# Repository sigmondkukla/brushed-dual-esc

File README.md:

# brushed-dual-esc
**Clarkson University Combat Robotics SPEED Team**

## Summary

Dual drive ESC for Clarkson Combat Robotics 1lb freshman PLAnt competition.
Supports two 3A brushed drive motors and includes a 5V 1A BEC output to power a receiver. 

## Details

The ESC implements an STM32C011 MCU to generate PWM for motor drivers from RX channel inputs while monitoring current, signal prescence (failsafe), and battery voltage UVLO.

With the 2026 revision of the ESC, XT30 wire-to-board connectors have been replaced with solder pads for leads to GNB A30 connectors.
An XT30 connector is still reccomended for the battery input.
The battery shall be a 2S or 3S LiPo battery; 4S is not supported based on cost optimization, though targeting a slightly higher cost (and larger size) by increasing capacitor specifications is a simple modification.
At 4S, the current from the 5V BEC output shall be kept to a minimum. 

The ESC expects two receiver channel outputs to be connected to the CH1 and CH2 inputs, which map directly to the DRV1 and DRV2 outputs. A 50 Hz (20 ms period) PWM signal (5V tolerated) with a duty cycle between 1000 us and 2000 us is needed, based on the outputs of the common FS-2A receiver.
A duty cycle of 1500 us is considered neutral, with lower duty cycles resulting in reverse operation and higher duty cycles corresponding to forward operation.

A 3A current limit has been configured with the 750-ohm resistors connected to IPROPI on each motor driver.
Above this current limit, the ESC will chop to avoid over current, despite the driver supporting up to 3.7A.
The ESC pairs well therefore with the [Repeat Mini Brushed Mk2](https://repeat-robotics.com/products/repeat-mini-brushed-mk2-1pcs), which has a stall current of 2A at 3S.

## Assembly

Assembly with a pick-and-place machine is reccomended for large volumes >= 10 units, though hand assembly is straightforward given the large motor driver, LDO, and passives packages.
The pick and place work file for a CHM-T36VA machine is included in the `pcb/fabrication` directory, though minor modifications may be necessary.
The DRV8231 ICs were not successfully picked by the machine so are set to be skipped, and the electrolytic capacitors were not attempted.
I loaded the 503 nozzle in tool 1 and the 505 nozzle in tool 2 for this job.

A clean paste image is necessary for successful soldering of the STM32 MCU.

## Programming

Programming is achieved through a Tag-Connect TC2030-CTX-NL pogo pins programmer cable which retails around $50, though can be purchased on Aliexpress for about half the price.
I'm using it in conjunction with a Segger J-Link EDU mini though any debugger can be used.
SWO is not available on STM32C0 so one of the six pins is unused.

The firmware may be programmed using [STM32CubeProg](https://www.st.com/en/development-tools/stm32cubeprog.html) and the firmware ELF file included in the most recent release on GitHub.

## Images
### Screenshots

### Photos

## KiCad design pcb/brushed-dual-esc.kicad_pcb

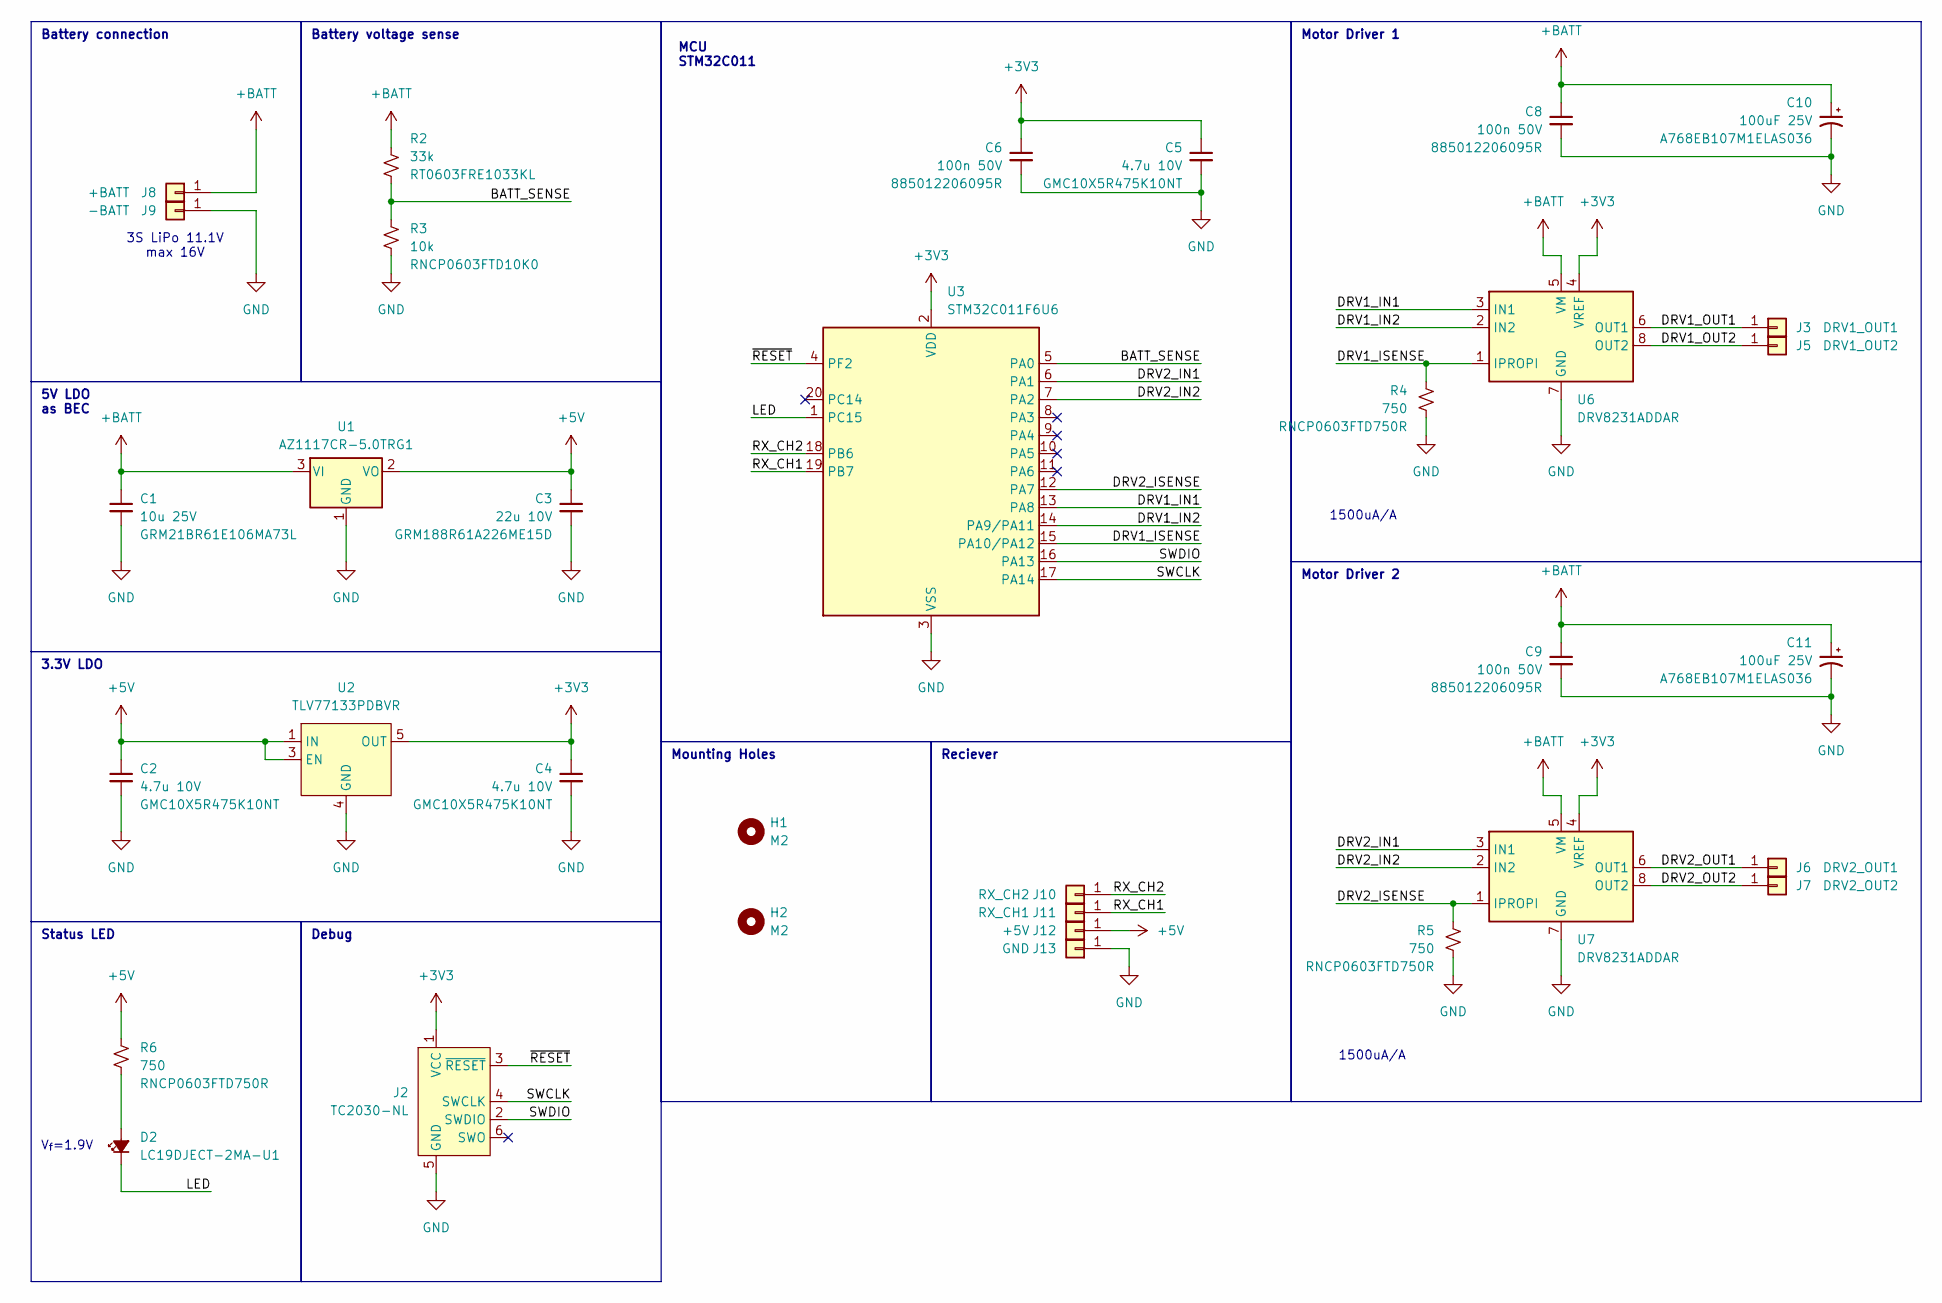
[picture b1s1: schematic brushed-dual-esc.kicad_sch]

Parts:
C1: 10u 25V; C_0805_2012Metric; MPN GRM21BR61E106MA73L
C2, C4, C5: 4.7u 10V; C_0603_1608Metric; MPN GMC10X5R475K10NT
C3: 22u 10V; C_0603_1608Metric; MPN GRM188R61A226ME15D
C6, C8, C9: 100n 50V; C_0603_1608Metric; MPN 885012206095R
C10, C11: 100uF 25V; CP_Elec_6.3x5.7; MPN A768EB107M1ELAS036
D2: LC19DJECT-2MA-U1; LED_0603_1608Metric; MPN LC19DJECT-2MA-U1
H1, H2: M2; MountingHole_2.2mm_M2
J2: TC2030-NL; Tag-Connect_TC2030-IDC-NL_2x03_P1.27mm_Vertical
J3: DRV1_OUT1; SolderWirePad_1x01_SMD_2x4mm
J5: DRV1_OUT2; SolderWirePad_1x01_SMD_2x4mm
J6: DRV2_OUT1; SolderWirePad_1x01_SMD_2x4mm
J7: DRV2_OUT2; SolderWirePad_1x01_SMD_2x4mm
J8: +BATT; SolderWirePad_1x01_SMD_2x4mm
J9: -BATT; SolderWirePad_1x01_SMD_2x4mm
J10: RX_CH2; SolderWirePad_1x01_SMD_1x2mm
J11: RX_CH1; SolderWirePad_1x01_SMD_1x2mm
J12: +5V; SolderWirePad_1x01_SMD_1x2mm
J13: GND; SolderWirePad_1x01_SMD_1x2mm
R2: 33k; R_0603_1608Metric; MPN RT0603FRE1033KL
R3: 10k; R_0603_1608Metric; MPN RNCP0603FTD10K0
R4, R5, R6: 750; R_0603_1608Metric; MPN RNCP0603FTD750R
U1: AZ1117CR-5.0TRG1; SOT-89-3; MPN AZ1117CR-5.0TRG1
U2: TLV77133PDBVR; SOT-23-5; MPN TLV77133PDBVR
U3: STM32C011F6U6; ST_UFQFPN-20_3x3mm_P0.5mm; MPN STM32C011F6U6
U6, U7: DRV8231ADDAR; Texas_HSOP-8-1EP_3.9x4.9mm_P1.27mm; MPN DRV8231ADDAR

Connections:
+3V3: C4.1, C5.1, C6.1, J2.1 (VCC), U2.5 (OUT), U3.2 (VDD), U6.4 (VREF), U7.4 (VREF)
+5V: C2.1, C3.1, J12.1 (Pin_1_1), R6.1, U1.2 (VO), U2.1 (IN), U2.3 (EN)
+BATT: C1.1, C8.1, C9.1, C10.1, C11.1, J8.1 (Pin_1_1), R2.1, U1.3 (VI), U6.5 (VM), U7.5 (VM)
/BATT_SENSE: R2.2, R3.1, U3.5 (PA0)
/DRV1_IN1: U3.13 (PA8), U6.3 (IN1)
/DRV1_IN2: U3.14 (PA9/PA11), U6.2 (IN2)
/DRV1_ISENSE: R4.1, U3.15 (PA10/PA12), U6.1 (IPROPI)
/DRV1_OUT1: J3.1 (Pin_1_1), U6.6 (OUT1)
/DRV1_OUT2: J5.1 (Pin_1_1), U6.8 (OUT2)
/DRV2_IN1: U3.6 (PA1), U7.3 (IN1)
/DRV2_IN2: U3.7 (PA2), U7.2 (IN2)
/DRV2_ISENSE: R5.1, U3.12 (PA7), U7.1 (IPROPI)
/DRV2_OUT1: J6.1 (Pin_1_1), U7.6 (OUT1)
/DRV2_OUT2: J7.1 (Pin_1_1), U7.8 (OUT2)
/LED: D2.1 (K), U3.1 (PC15)
/RX_CH1: J11.1 (Pin_1_1), U3.19 (PB7)
/RX_CH2: J10.1 (Pin_1_1), U3.18 (PB6)
/SWCLK: J2.4 (SWCLK), U3.17 (PA14)
/SWDIO: J2.2 (SWDIO), U3.16 (PA13)
/~RESET: J2.3 (~RESET), U3.4 (PF2)
GND: C1.2, C2.2, C3.2, C4.2, C5.2, C6.2, C8.2, C9.2, C10.2, C11.2, J2.5 (GND), J9.1 (Pin_1_1), J13.1 (Pin_1_1), R3.2, R4.2, R5.2, U1.1 (GND), U2.4 (GND), U3.3 (VSS), U6.7 (GND), U6.9 (GND), U7.7 (GND), U7.9 (GND)
unnamed: D2.2 (A), R6.2

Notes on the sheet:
3.3V LDO
Status LED
Motor Driver 1
Motor Driver 2
Mounting Holes
1500uA/A
5V LDO as BEC
V_{f}=1.9V
Battery connection
Battery voltage sense
MCU STM32C011
3S LiPo 11.1V max 16V
Reciever
Debug

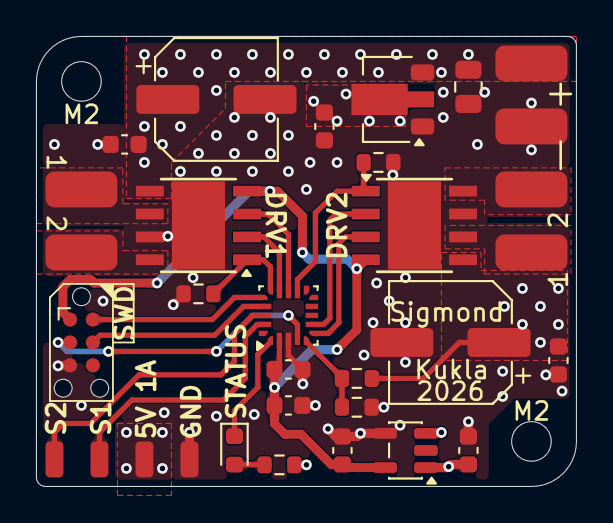
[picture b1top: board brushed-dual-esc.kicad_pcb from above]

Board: 2 copper layers, 30.0 x 25.0 mm, 34 parts (0 on the bottom side), 22 nets.

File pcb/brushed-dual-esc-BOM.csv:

"Reference","Qty","Value","MPN"
"C1","1","10µF 25V","GRM21BR61E106MA73L"
"C2,C4,C5","3","4.7u 10V","GMC10X5R475K10NT"
"C3","1","22uF 10V","GRM188R61A226ME15D"
"C6,C8,C9","3","100n 50V","885012206095R"
"C10,C11","2","100uF 25V","A768EB107M1ELAS036"
"D2","1","Vf=1.9V","LC19DJECT-2MA-U1"
"R2","1","33k","RT0603FRE1033KL"
"R3","1","10k","RNCP0603FTD10K0"
"R4,R5,R6","3","750","RNCP0603FTD750R"
"U1","1","AZ1117CR-5.0TRG1","AZ1117CR-5.0TRG1"
"U2","1","TLV77133PDBVR","TLV77133PDBVR"
"U3","1","STM32C011F6U6","STM32C011F6U6"
"U6,U7","2","DRV8231ADDAR","DRV8231ADDAR"

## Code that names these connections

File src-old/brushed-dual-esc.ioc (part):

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Mcu.Name=STM32C011F(4-6)Ux
Mcu.Package=UFQFPN20
Mcu.UserName=STM32C011F4Ux
PA0.GPIOParameters=GPIO_PuPd,GPIO_Label,GPIO_Mode
PA0.GPIO_Label=BATT_SENSE
PA0.GPIO_Mode=GPIO_MODE_ANALOG
PA0.GPIO_PuPd=GPIO_NOPULL
PA0.Mode=IN0
PA0.Signal=ADC1_IN0
PA1.GPIOParameters=GPIO_PuPd,GPIO_Label
PA1.GPIO_Label=DRV2_IN1
PA1.GPIO_PuPd=GPIO_PULLDOWN
PA1.Signal=S_TIM1_CH2
PA11\ [PA9].GPIOParameters=GPIO_PuPd,GPIO_Label
PA11\ [PA9].GPIO_Label=DRV1_IN2
PA11\ [PA9].GPIO_PuPd=GPIO_PULLDOWN
PA11\ [PA9].Signal=S_TIM1_CH4
PA12\ [PA10].GPIOParameters=GPIO_PuPd,GPIO_Label,GPIO_Mode
PA12\ [PA10].GPIO_Label=DRV1_ISENSE
PA12\ [PA10].GPIO_Mode=GPIO_MODE_ANALOG
PA12\ [PA10].GPIO_PuPd=GPIO_NOPULL
PA12\ [PA10].Mode=IN12
PA12\ [PA10].Signal=ADC1_IN12
PA13.Mode=Serial_Wire
PA13.Signal=DEBUG_SWDIO
PA14-BOOT0.Mode=Serial_Wire
PA14-BOOT0.Signal=DEBUG_SWCLK
PA2.GPIOParameters=GPIO_PuPd,GPIO_Label
PA2.GPIO_Label=DRV2_IN2
PA2.GPIO_PuPd=GPIO_PULLDOWN
PA2.Signal=S_TIM1_CH3
PA7.GPIOParameters=GPIO_PuPd,GPIO_Label,GPIO_Mode
PA7.GPIO_Label=DRV2_ISENSE
PA7.GPIO_Mode=GPIO_MODE_ANALOG
PA7.GPIO_PuPd=GPIO_NOPULL
PA7.Mode=IN7
PA7.Signal=ADC1_IN7
PA8.GPIOParameters=GPIO_PuPd,GPIO_Label
PA8.GPIO_Label=DRV1_IN1
PA8.GPIO_PuPd=GPIO_PULLDOWN
PA8.Signal=S_TIM1_CH1
PB6.GPIOParameters=GPIO_PuPd,GPIO_Label
PB6.GPIO_Label=RX_CH2
PB6.GPIO_PuPd=GPIO_PULLDOWN
PB6.Signal=S_TIM3_CH2
PB7.GPIOParameters=GPIO_PuPd,GPIO_Label
PB7.GPIO_Label=RX_CH1
PB7.GPIO_PuPd=GPIO_PULLDOWN
PB7.Signal=S_TIM3_CH1
PC15-OSCX_OUT\ (PC15).GPIOParameters=GPIO_Label
PC15-OSCX_OUT\ (PC15).GPIO_Label=LED
PC15-OSCX_OUT\ (PC15).Signal=GPIO_Output
RCC.HSE_VALUE=8000000
RCC.SYSCLKFreq_VALUE=12000000
board=custom

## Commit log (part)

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2025-08-24 Finish design
2025-08-24 Add images
2025-08-24 Add README
2025-08-26 Add status LED on spare pin
2025-08-26 Create 3V3 zone in top left
2025-08-26 Generate ibom
2025-08-26 Adjust 5V LDO ground plane placement
2025-08-26 Increase top GND zone size for LDO
2025-08-27 Fix capacitor siutation
2025-08-27 Update footprints
2025-08-27 Add testpoints and imrpove silkscreen
2025-09-18 Add step file
2025-10-26 Semi-working ESC firmware
2025-10-26 Add neutral braking functionality
